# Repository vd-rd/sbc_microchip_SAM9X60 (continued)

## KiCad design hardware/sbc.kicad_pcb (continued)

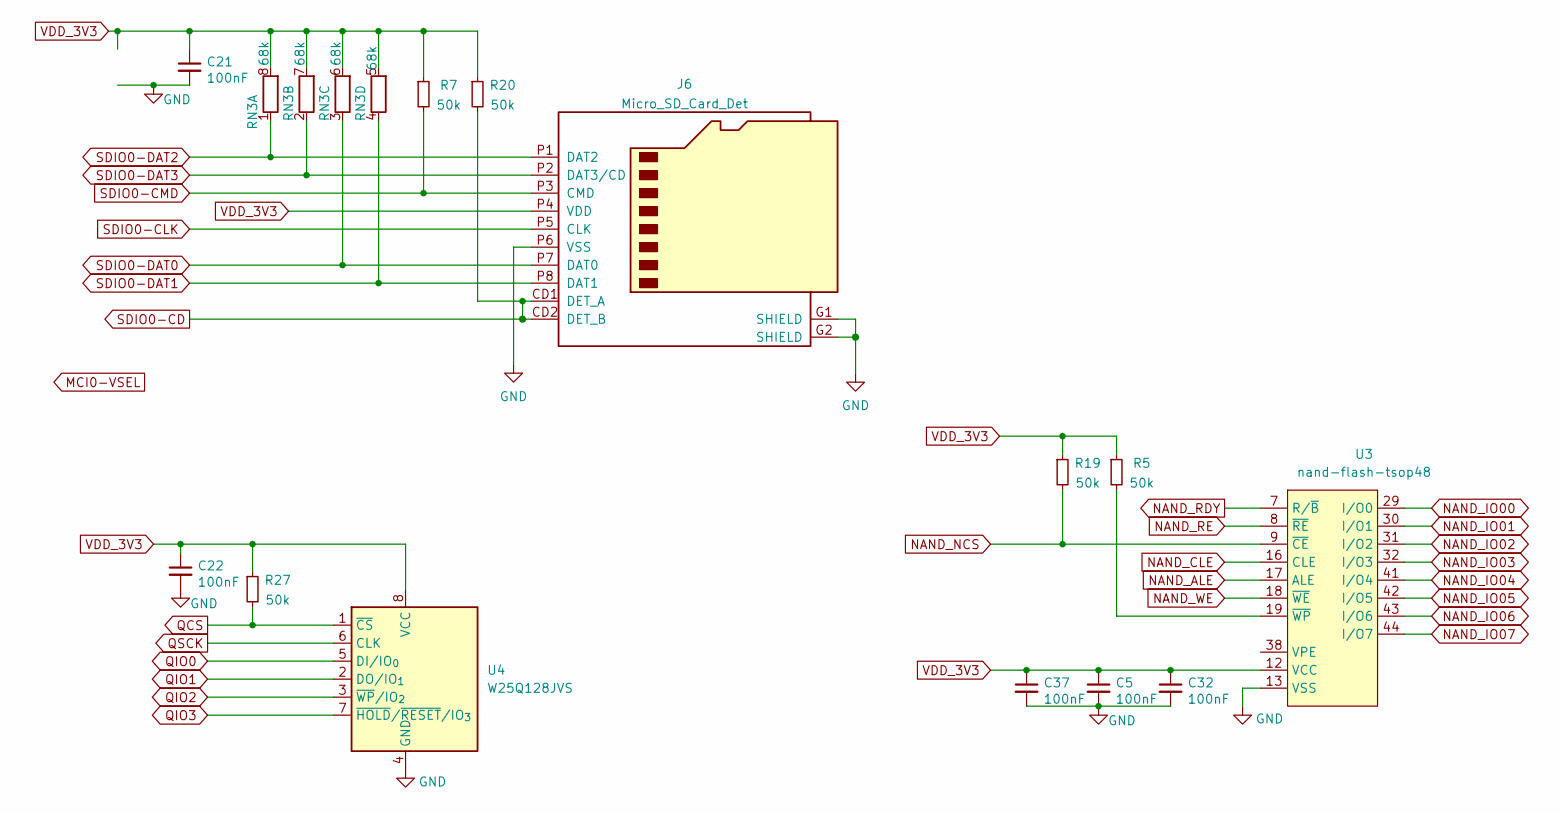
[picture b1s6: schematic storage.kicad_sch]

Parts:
C5, C21, C22, C32, C37: 100nF; C_0402_1005Metric
J6: Micro_SD_Card_Det; MEM20610118800A
R5, R7, R19, R20, R27: 50k; R_0402_1005Metric
RN3: 68k; R_Array_Concave_4x0402
U3: nand-flash-tsop48; TSOP-I-48_18.4x12mm_P0.5mm
U4: W25Q128JVS; SOIC-8_5.3x5.3mm_P1.27mm

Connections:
NAND_ALE: U3.17 (ALE); also elsewhere on the board
NAND_CLE: U3.16 (CLE); also elsewhere on the board
NAND_IO00: U3.29 (I/O0); also elsewhere on the board
NAND_IO01: U3.30 (I/O1); also elsewhere on the board
NAND_IO02: U3.31 (I/O2); also elsewhere on the board
NAND_IO03: U3.32 (I/O3); also elsewhere on the board
NAND_IO04: U3.41 (I/O4); also elsewhere on the board
NAND_IO05: U3.42 (I/O5); also elsewhere on the board
NAND_IO06: U3.43 (I/O6); also elsewhere on the board
NAND_IO07: U3.44 (I/O7); also elsewhere on the board
NAND_NCS: R19.2, U3.9 (~CE); also elsewhere on the board
NAND_RDY: U3.7 (R/~B); also elsewhere on the board
NAND_RE: U3.8 (~RE); also elsewhere on the board
NAND_WE: U3.18 (~WE); also elsewhere on the board
unnamed: R5.2, U3.19 (~WP)
QCS: R27.2, U4.1 (~CS); also elsewhere on the board
QIO0: U4.5 (DI/IO_{0}); also elsewhere on the board
QIO1: U4.2 (DO/IO_{1}); also elsewhere on the board
QIO2: U4.3 (~WP/IO_{2}); also elsewhere on the board
QIO3: U4.7 (~HOLD/~RESET/IO_{3}); also elsewhere on the board
QSCK: U4.6 (CLK); also elsewhere on the board
SDIO0-CD: J6.CD1 (DET_A), J6.CD2 (DET_B), R20.2; also elsewhere on the board
SDIO0-CLK: J6.P5 (CLK); also elsewhere on the board
SDIO0-CMD: J6.P3 (CMD), R7.2; also elsewhere on the board
SDIO0-DAT0: J6.P7 (DAT0), RN3.3 (R3.1); also elsewhere on the board
SDIO0-DAT1: J6.P8 (DAT1), RN3.4 (R4.1); also elsewhere on the board
SDIO0-DAT2: J6.P1 (DAT2), RN3.1 (R1.1); also elsewhere on the board
SDIO0-DAT3: J6.P2 (DAT3/CD), RN3.2 (R2.1); also elsewhere on the board
VDD_3V3: C5.1, C21.1, C22.1, C32.1, C37.1, J6.P4 (VDD), R5.1, R7.1, R19.1, R20.1, R27.1, RN3.5 (R4.2), RN3.6 (R3.2), RN3.7 (R2.2), RN3.8 (R1.2), U3.12 (VCC), U3.34 (VCC), U3.37 (VCC), U3.39 (VCC), U4.8 (VCC); also elsewhere on the board

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
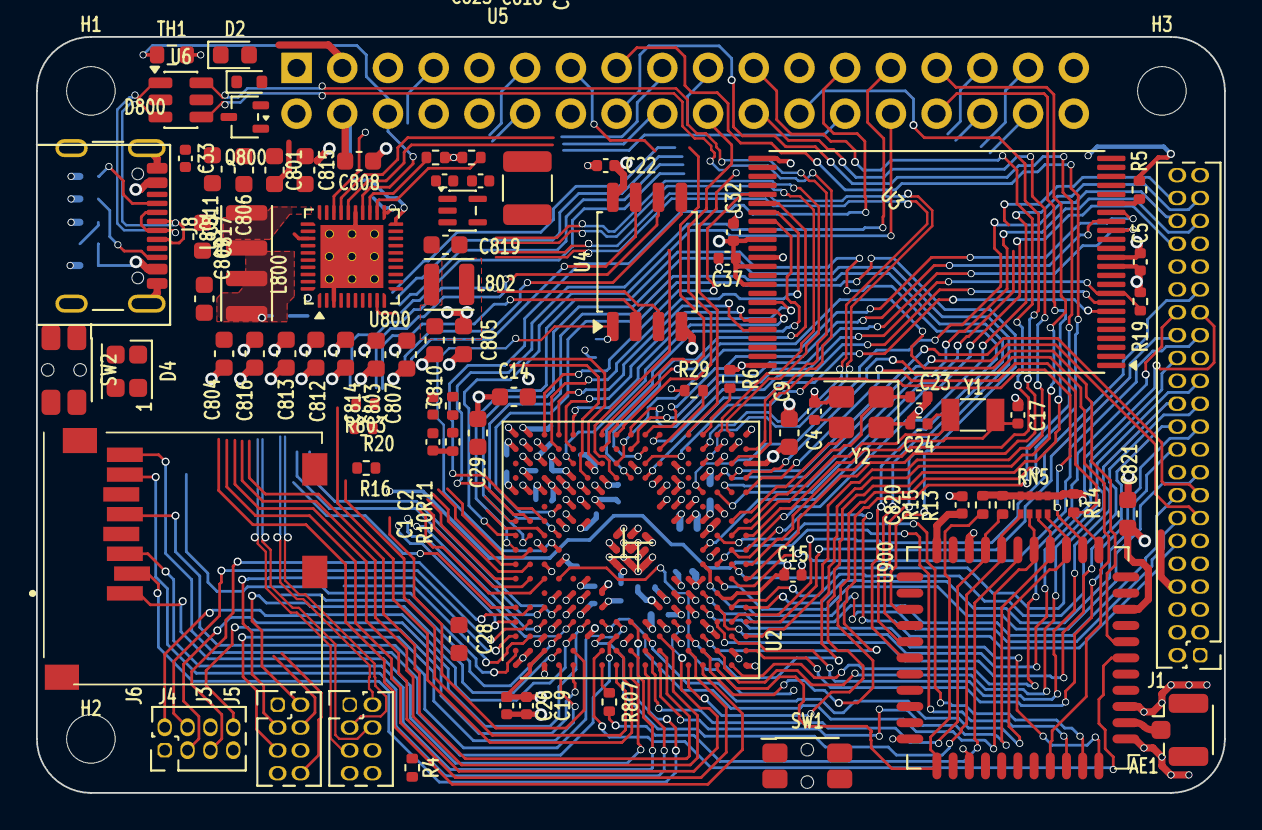
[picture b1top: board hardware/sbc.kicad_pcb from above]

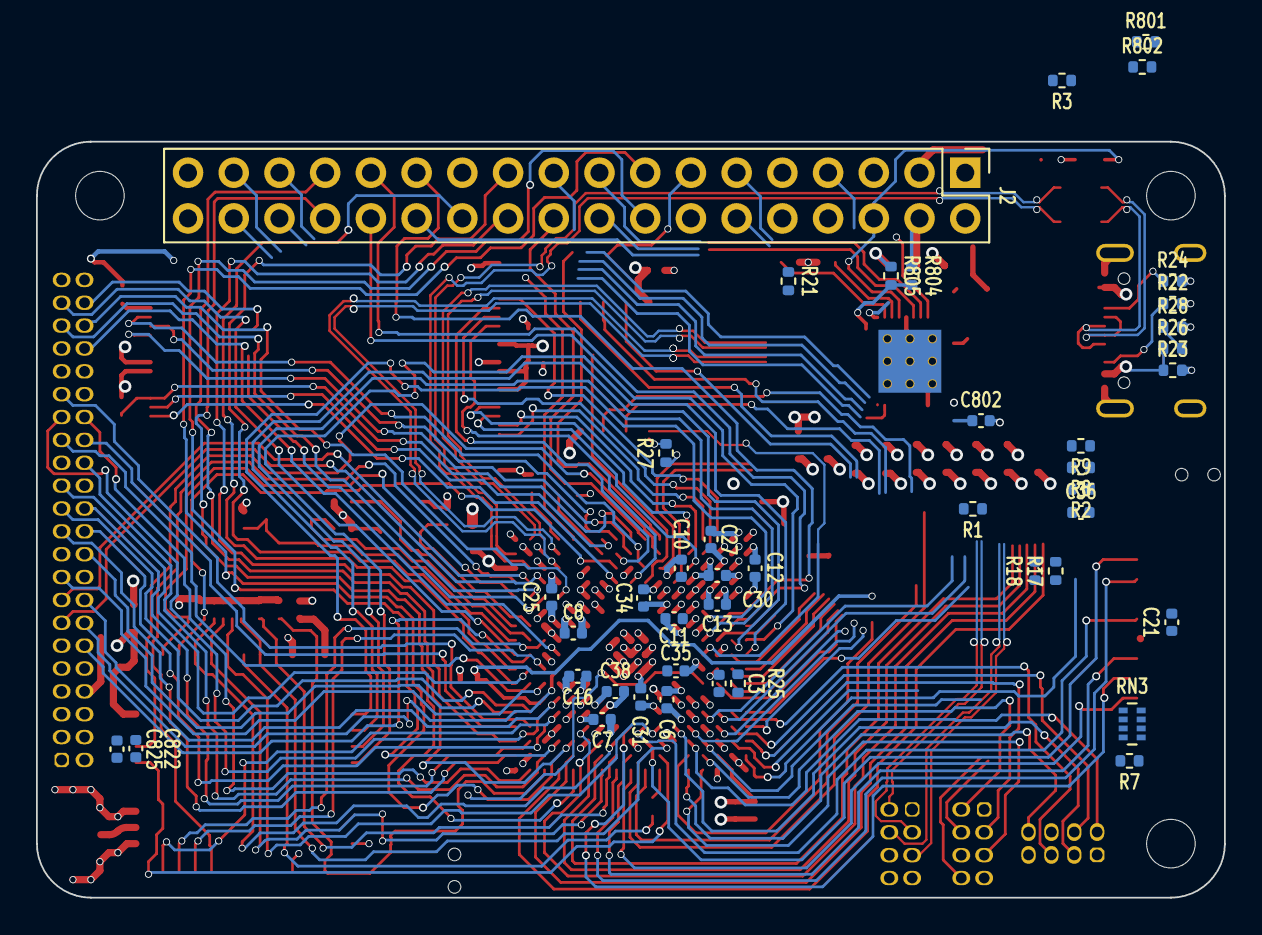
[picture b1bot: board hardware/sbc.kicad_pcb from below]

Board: 4 copper layers, 66.0 x 42.0 mm, 129 parts (43 on the bottom side), 165 nets.

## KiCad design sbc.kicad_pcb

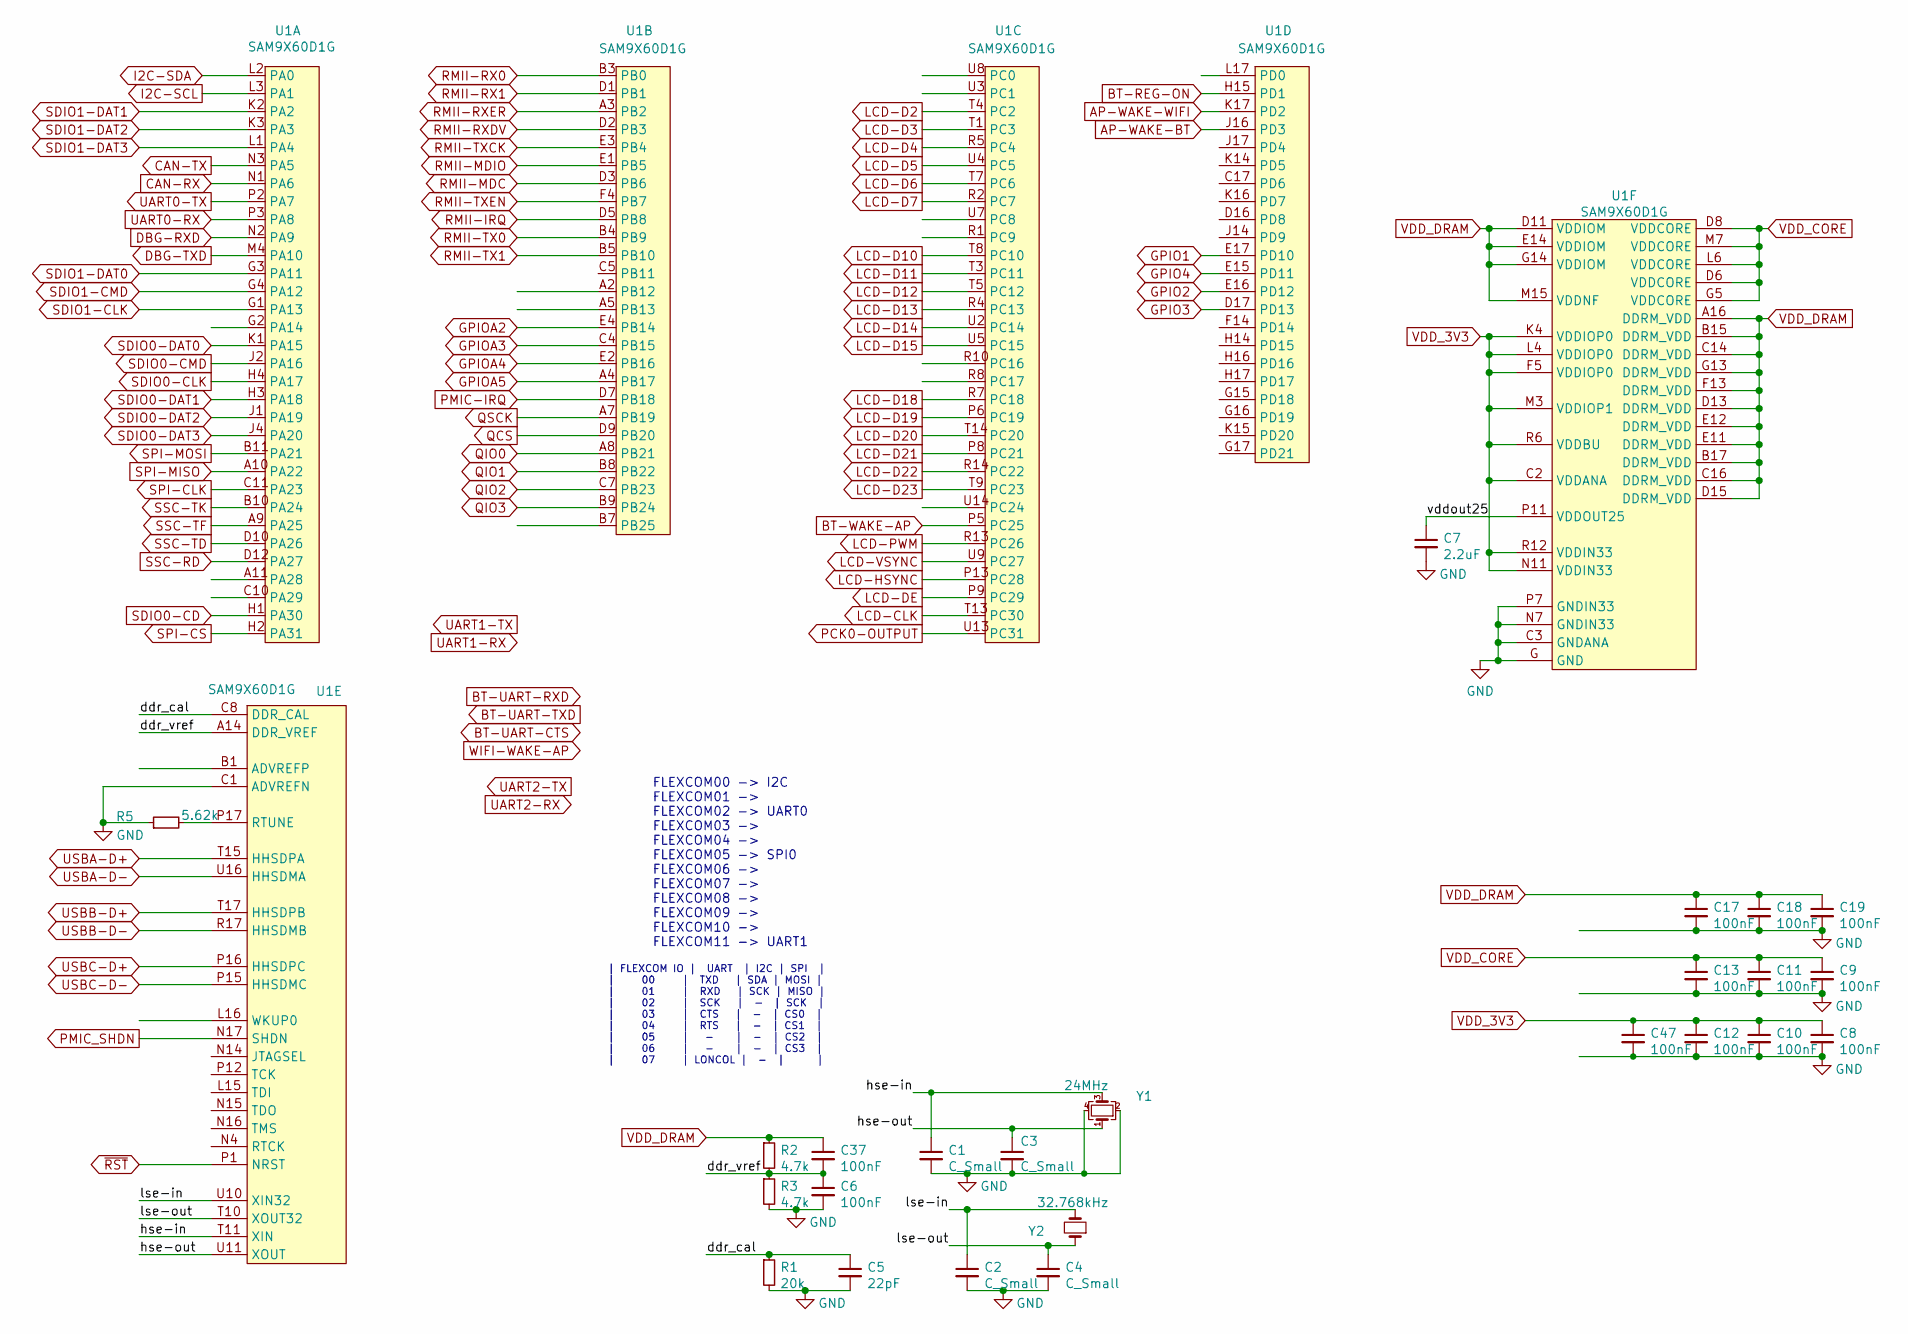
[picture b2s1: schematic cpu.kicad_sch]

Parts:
C1, C2, C3, C4: C_Small; C_0402_1005Metric
C5: 22pF; C_0402_1005Metric
C6, C8, C9, C10, C11, C12, C13, C17, C18, C19, C37, C47: 100nF; C_0402_1005Metric
C7: 2.2uF; C_0402_1005Metric
R1: 20k; R_0402_1005Metric
R2, R3: 4.7k; R_0402_1005Metric
R5: 5.62k; R_0402_1005Metric
U1: SAM9X60D1G
Y1: 24MHz; Crystal_SMD_3225-4Pin_3.2x2.5mm
Y2: 32.768kHz; Crystal_SMD_3215-2Pin_3.2x1.5mm

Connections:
/cpu/ddr_cal: C5.1, R1.1, U1.C8 (DDR_CAL)
/cpu/ddr_vref: C6.1, C37.2, R2.2, R3.1, U1.A14 (DDR_VREF)
/cpu/hse-in: C1.1, U1.T11 (XIN), Y1.3
/cpu/hse-out: C3.1, U1.U11 (XOUT), Y1.1
/cpu/lse-in: C2.1, U1.U10 (XIN32), Y2.2
/cpu/lse-out: C4.1, U1.T10 (XOUT32), Y2.1
/cpu/vddout25: C7.1, U1.P11 (VDDOUT25)
AP-WAKE-BT: U1.J16 (PD3); also elsewhere on the board
AP-WAKE-WIFI: U1.K17 (PD2); also elsewhere on the board
BT-REG-ON: U1.H15 (PD1); also elsewhere on the board
BT-WAKE-AP: U1.P5 (PC25); also elsewhere on the board
CAN-RX: U1.N1 (PA6); also elsewhere on the board
CAN-TX: U1.N3 (PA5); also elsewhere on the board
DBG-RXD: U1.N2 (PA9); also elsewhere on the board
DBG-TXD: U1.M4 (PA10); also elsewhere on the board
GND: C1.2, C2.2, C3.2, C4.2, C5.2, C6.2, C7.2, C8.2, C9.2, C10.2, C11.2, C12.2, C13.2, C17.2, C18.2, C19.2, C47.2, R1.2, R3.2, R5.1, U1.C1 (ADVREFN), U1.C3 (GNDANA), U1.G (GND), U1.N7 (GNDIN33), U1.P7 (GNDIN33), Y1.2, Y1.4; also elsewhere on the board
GPIO1: U1.E17 (PD10); also elsewhere on the board
GPIO2: U1.E16 (PD12); also elsewhere on the board
GPIO3: U1.D17 (PD13); also elsewhere on the board
GPIO4: U1.E15 (PD11); also elsewhere on the board
GPIOA2: U1.E4 (PB14); also elsewhere on the board
GPIOA3: U1.C4 (PB15); also elsewhere on the board
GPIOA4: U1.E2 (PB16); also elsewhere on the board
GPIOA5: U1.A4 (PB17); also elsewhere on the board
I2C-SCL: U1.L3 (PA1); also elsewhere on the board
I2C-SDA: U1.L2 (PA0); also elsewhere on the board
LCD-CLK: U1.T13 (PC30); also elsewhere on the board
LCD-D2: U1.T4 (PC2); also elsewhere on the board
LCD-D3: U1.T1 (PC3); also elsewhere on the board
LCD-D4: U1.R5 (PC4); also elsewhere on the board
LCD-D5: U1.U4 (PC5); also elsewhere on the board
LCD-D6: U1.T7 (PC6); also elsewhere on the board
LCD-D7: U1.R2 (PC7); also elsewhere on the board
LCD-D10: U1.T8 (PC10); also elsewhere on the board
LCD-D11: U1.T3 (PC11); also elsewhere on the board
LCD-D12: U1.T5 (PC12); also elsewhere on the board
LCD-D13: U1.R4 (PC13); also elsewhere on the board
LCD-D14: U1.U2 (PC14); also elsewhere on the board
LCD-D15: U1.U5 (PC15); also elsewhere on the board
LCD-D18: U1.R7 (PC18); also elsewhere on the board
LCD-D19: U1.P6 (PC19); also elsewhere on the board
LCD-D20: U1.T14 (PC20); also elsewhere on the board
LCD-D21: U1.P8 (PC21); also elsewhere on the board
LCD-D22: U1.R14 (PC22); also elsewhere on the board
LCD-D23: U1.T9 (PC23); also elsewhere on the board
LCD-DE: U1.P9 (PC29); also elsewhere on the board
LCD-HSYNC: U1.P13 (PC28); also elsewhere on the board
LCD-PWM: U1.R13 (PC26)
LCD-VSYNC: U1.U9 (PC27); also elsewhere on the board
unnamed: R5.2, U1.P17 (RTUNE)
PCK0-OUTPUT: U1.U13 (PC31); also elsewhere on the board
PMIC-IRQ: U1.D7 (PB18); also elsewhere on the board
PMIC_SHDN: U1.N17 (SHDN)
QCS: U1.D9 (PB20); also elsewhere on the board
QIO0: U1.A8 (PB21); also elsewhere on the board
QIO1: U1.B8 (PB22); also elsewhere on the board
QIO2: U1.C7 (PB23); also elsewhere on the board
QIO3: U1.B9 (PB24); also elsewhere on the board
QSCK: U1.A7 (PB19); also elsewhere on the board
RMII-IRQ: U1.D5 (PB8)
RMII-MDC: U1.D3 (PB6); also elsewhere on the board
RMII-MDIO: U1.E1 (PB5); also elsewhere on the board
RMII-RX0: U1.B3 (PB0); also elsewhere on the board
RMII-RX1: U1.D1 (PB1); also elsewhere on the board
RMII-RXDV: U1.D2 (PB3); also elsewhere on the board
RMII-RXER: U1.A3 (PB2); also elsewhere on the board
RMII-TX0: U1.B4 (PB9); also elsewhere on the board
RMII-TX1: U1.B5 (PB10); also elsewhere on the board
RMII-TXCK: U1.E3 (PB4); also elsewhere on the board
RMII-TXEN: U1.F4 (PB7); also elsewhere on the board
SDIO0-CD: U1.H1 (PA30); also elsewhere on the board
SDIO0-CLK: U1.H4 (PA17); also elsewhere on the board
SDIO0-CMD: U1.J2 (PA16); also elsewhere on the board
SDIO0-DAT0: U1.K1 (PA15); also elsewhere on the board
SDIO0-DAT1: U1.H3 (PA18); also elsewhere on the board
SDIO0-DAT2: U1.J1 (PA19); also elsewhere on the board
SDIO0-DAT3: U1.J4 (PA20); also elsewhere on the board
SDIO1-CLK: U1.G1 (PA13); also elsewhere on the board
SDIO1-CMD: U1.G4 (PA12); also elsewhere on the board
SDIO1-DAT0: U1.G3 (PA11); also elsewhere on the board
SDIO1-DAT1: U1.K2 (PA2); also elsewhere on the board
SDIO1-DAT2: U1.K3 (PA3); also elsewhere on the board
SDIO1-DAT3: U1.L1 (PA4); also elsewhere on the board
SPI-CLK: U1.C11 (PA23); also elsewhere on the board
SPI-CS: U1.H2 (PA31); also elsewhere on the board
SPI-MISO: U1.A10 (PA22); also elsewhere on the board
SPI-MOSI: U1.B11 (PA21); also elsewhere on the board
SSC-RD: U1.D12 (PA27); also elsewhere on the board
SSC-TD: U1.D10 (PA26); also elsewhere on the board
SSC-TF: U1.A9 (PA25); also elsewhere on the board
SSC-TK: U1.B10 (PA24); also elsewhere on the board
UART0-RX: U1.P3 (PA8)
UART0-TX: U1.P2 (PA7)
USBA-D+: U1.T15 (HHSDPA); also elsewhere on the board
USBA-D-: U1.U16 (HHSDMA); also elsewhere on the board
USBB-D+: U1.T17 (HHSDPB)
USBB-D-: U1.R17 (HHSDMB)
USBC-D+: U1.P16 (HHSDPC)
USBC-D-: U1.P15 (HHSDMC)
VDD_3V3: C8.1, C10.1, C12.1, C47.1, U1.C2 (VDDANA), U1.F5 (VDDIOP0), U1.K4 (VDDIOP0), U1.L4 (VDDIOP0), U1.M3 (VDDIOP1), U1.N11 (VDDIN33), U1.R6 (VDDBU), U1.R12 (VDDIN33); also elsewhere on the board
VDD_CORE: C9.1, C11.1, C13.1, U1.D6 (VDDCORE), U1.D8 (VDDCORE), U1.G5 (VDDCORE), U1.L6 (VDDCORE), U1.M7 (VDDCORE); also elsewhere on the board
VDD_DRAM: C17.1, C18.1, C19.1, C37.1, R2.1, U1.A16 (DDRM_VDD), U1.B15 (DDRM_VDD), U1.B17 (DDRM_VDD), U1.C14 (DDRM_VDD), U1.C16 (DDRM_VDD), U1.D11 (VDDIOM), U1.D13 (DDRM_VDD), U1.D15 (DDRM_VDD), U1.E11 (DDRM_VDD), U1.E12 (DDRM_VDD), U1.E14 (VDDIOM), U1.F13 (DDRM_VDD), U1.G13 (DDRM_VDD), U1.G14 (VDDIOM), U1.M15 (VDDNF); also elsewhere on the board
~RST: U1.P1 (NRST); also elsewhere on the board

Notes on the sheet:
| FLEXCOM IO | UART | I2C | SPI | | 00 | TXD | SDA | MOSI | | 01 | RXD | SCK | MISO | | 02 | SCK | - | SCK | | 03 | CTS | - | CS0 | | 04 | RTS | - | CS1 | | 05 | - | - | CS2 | | 06 | - | - | CS3 | | 07 | LONCOL | - | |
FLEXCOM00 -> I2C FLEXCOM01 -> FLEXCOM02 -> UART0 FLEXCOM03 -> FLEXCOM04 -> FLEXCOM05 -> SPI0 FLEXCOM06 -> FLEXCOM07 -> FLEXCOM08 -> FLEXCOM09 -> FLEXCOM10 -> FLEXCOM11 -> UART1

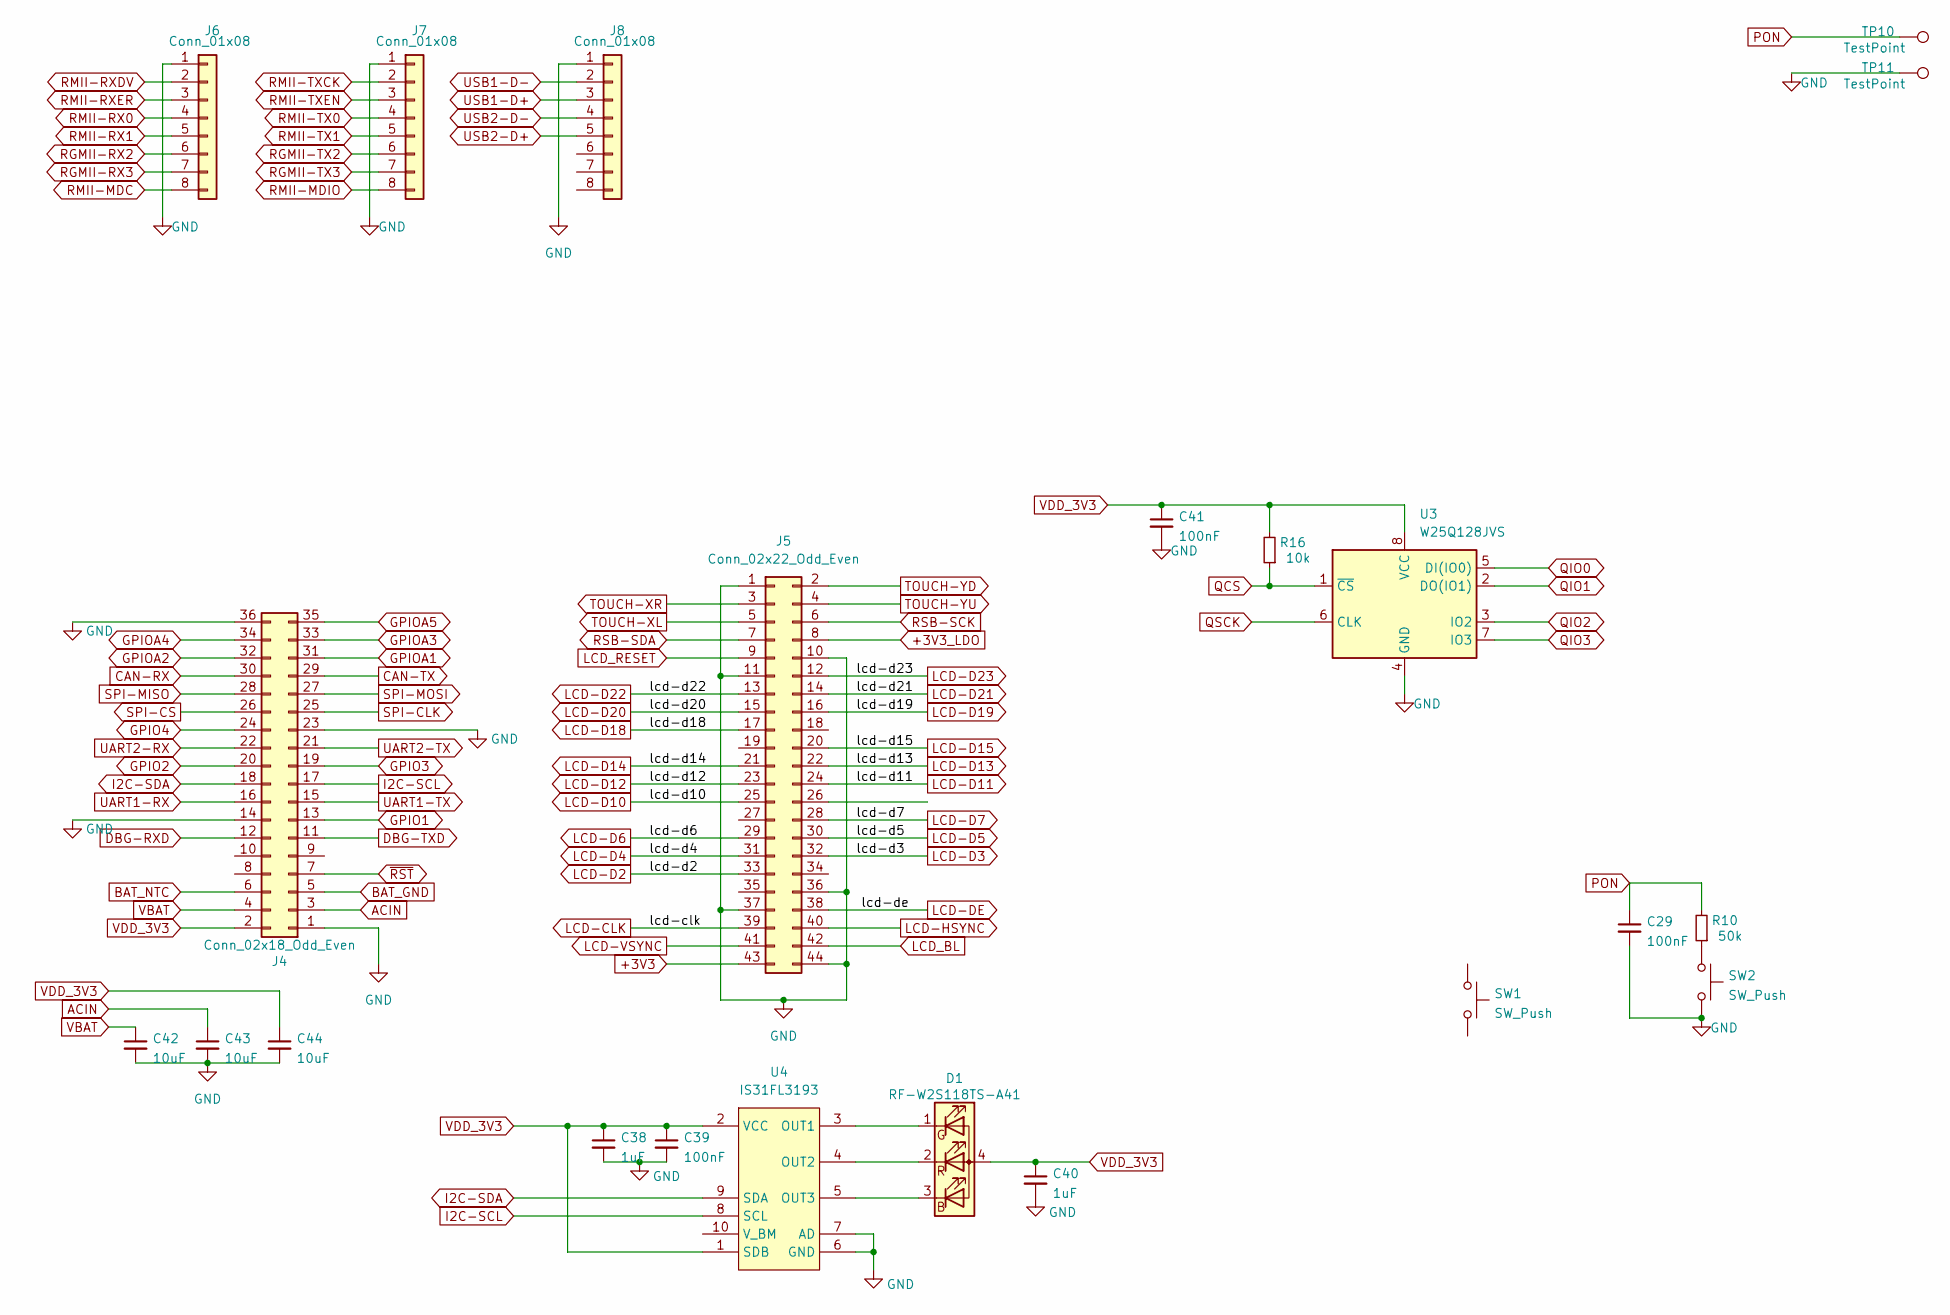
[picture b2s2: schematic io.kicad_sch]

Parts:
C29, C39, C41: 100nF; C_0402_1005Metric
C38, C40: 1uF; C_0402_1005Metric
C42, C43, C44: 10uF; C_0805_2012Metric
D1: RF-W2S118TS-A41; rgb-1204
J4: Conn_02x18_Odd_Even; PinHeader_2x18_P2.54mm_Vertical
J5: Conn_02x22_Odd_Even; PinHeader_2x22_P1.27mm_Vertical
J6, J7, J8: Conn_01x08; PinHeader_2x04_P1.27mm_Vertical
R10: 50k; R_0402_1005Metric
R16: 10k; R_0402_1005Metric
SW1, SW2: SW_Push; SW_SPST_EVQP7C
TP10, TP11: TestPoint; TestPoint_Pad_D1.0mm
U3: W25Q128JVS; SOIC-8_5.23x5.23mm_P1.27mm
U4: IS31FL3193; DFN-10-1EP_3x3mm_P0.5mm_EP1.7x2.5mm

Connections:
+3V3: J5.43
+3V3_LDO: J5.8
ACIN: C43.1, J4.3; also elsewhere on the board
BAT_GND: J4.5
BAT_NTC: J4.6; also elsewhere on the board
CAN-RX: J4.30; also elsewhere on the board
CAN-TX: J4.29; also elsewhere on the board
DBG-RXD: J4.12; also elsewhere on the board
DBG-TXD: J4.11; also elsewhere on the board
GND: C29.2, C38.2, C39.2, C40.2, C41.2, C42.2, C43.2, C44.2, J4.1, J4.14, J4.23, J4.36, J5.1, J5.10, J5.11, J5.36, J5.37, J5.44, J6.1, J7.1, J8.1, SW2.2, TP11.1, U3.4 (GND), U4.6 (GND), U4.7 (AD), U4.11 (GND); also elsewhere on the board
GPIO1: J4.13; also elsewhere on the board
GPIO2: J4.20; also elsewhere on the board
GPIO3: J4.19; also elsewhere on the board
GPIO4: J4.24; also elsewhere on the board
GPIOA1: J4.31
GPIOA2: J4.32; also elsewhere on the board
GPIOA3: J4.33; also elsewhere on the board
GPIOA4: J4.34; also elsewhere on the board
GPIOA5: J4.35; also elsewhere on the board
I2C-SCL: J4.17, U4.8 (SCL); also elsewhere on the board
I2C-SDA: J4.18, U4.9 (SDA); also elsewhere on the board
LCD-CLK: J5.39; also elsewhere on the board
LCD-D2: J5.33; also elsewhere on the board
LCD-D3: J5.32; also elsewhere on the board
LCD-D4: J5.31; also elsewhere on the board
LCD-D5: J5.30; also elsewhere on the board
LCD-D6: J5.29; also elsewhere on the board
LCD-D7: J5.28; also elsewhere on the board
LCD-D10: J5.25; also elsewhere on the board
LCD-D11: J5.24; also elsewhere on the board
LCD-D12: J5.23; also elsewhere on the board
LCD-D13: J5.22; also elsewhere on the board
LCD-D14: J5.21; also elsewhere on the board
LCD-D15: J5.20; also elsewhere on the board
LCD-D18: J5.17; also elsewhere on the board
LCD-D19: J5.16; also elsewhere on the board
LCD-D20: J5.15; also elsewhere on the board
LCD-D21: J5.14; also elsewhere on the board
LCD-D22: J5.13; also elsewhere on the board
LCD-D23: J5.12; also elsewhere on the board
LCD-DE: J5.38; also elsewhere on the board
LCD-HSYNC: J5.40; also elsewhere on the board
LCD-VSYNC: J5.41; also elsewhere on the board
LCD_BL: J5.42
LCD_RESET: J5.9
unnamed: D1.3 (BK), U4.5 (OUT3)
unnamed: D1.1 (GK), U4.3 (OUT1)
unnamed: D1.2 (RK), U4.4 (OUT2)
unnamed: R10.1, SW2.1
PON: C29.1, R10.2, TP10.1; also elsewhere on the board
QCS: R16.1, U3.1 (~CS); also elsewhere on the board
QIO0: U3.5 (DI(IO0)); also elsewhere on the board
QIO1: U3.2 (DO(IO1)); also elsewhere on the board
QIO2: U3.3 (IO2); also elsewhere on the board
QIO3: U3.7 (IO3); also elsewhere on the board
QSCK: U3.6 (CLK); also elsewhere on the board
RGMII-RX2: J6.6
RGMII-RX3: J6.7
RGMII-TX2: J7.6
RGMII-TX3: J7.7
RMII-MDC: J6.8; also elsewhere on the board
RMII-MDIO: J7.8; also elsewhere on the board
RMII-RX0: J6.4; also elsewhere on the board
RMII-RX1: J6.5; also elsewhere on the board
RMII-RXDV: J6.2; also elsewhere on the board
RMII-RXER: J6.3; also elsewhere on the board
RMII-TX0: J7.4; also elsewhere on the board
RMII-TX1: J7.5; also elsewhere on the board
RMII-TXCK: J7.2; also elsewhere on the board
RMII-TXEN: J7.3; also elsewhere on the board
RSB-SCK: J5.6
RSB-SDA: J5.7
SPI-CLK: J4.25; also elsewhere on the board
SPI-CS: J4.26; also elsewhere on the board
SPI-MISO: J4.28; also elsewhere on the board
SPI-MOSI: J4.27; also elsewhere on the board
TOUCH-XL: J5.5
TOUCH-XR: J5.3
TOUCH-YD: J5.2
TOUCH-YU: J5.4
UART1-RX: J4.16
UART1-TX: J4.15
UART2-RX: J4.22
UART2-TX: J4.21
USB1-D+: J8.3
USB1-D-: J8.2
USB2-D+: J8.5
USB2-D-: J8.4
VBAT: C42.1, J4.4; also elsewhere on the board
VDD_3V3: C38.1, C39.1, C40.1, C41.1, C44.1, D1.4 (A), J4.2, R16.2, U3.8 (VCC), U4.1 (SDB), U4.2 (VCC); also elsewhere on the board
~RST: J4.7; also elsewhere on the board

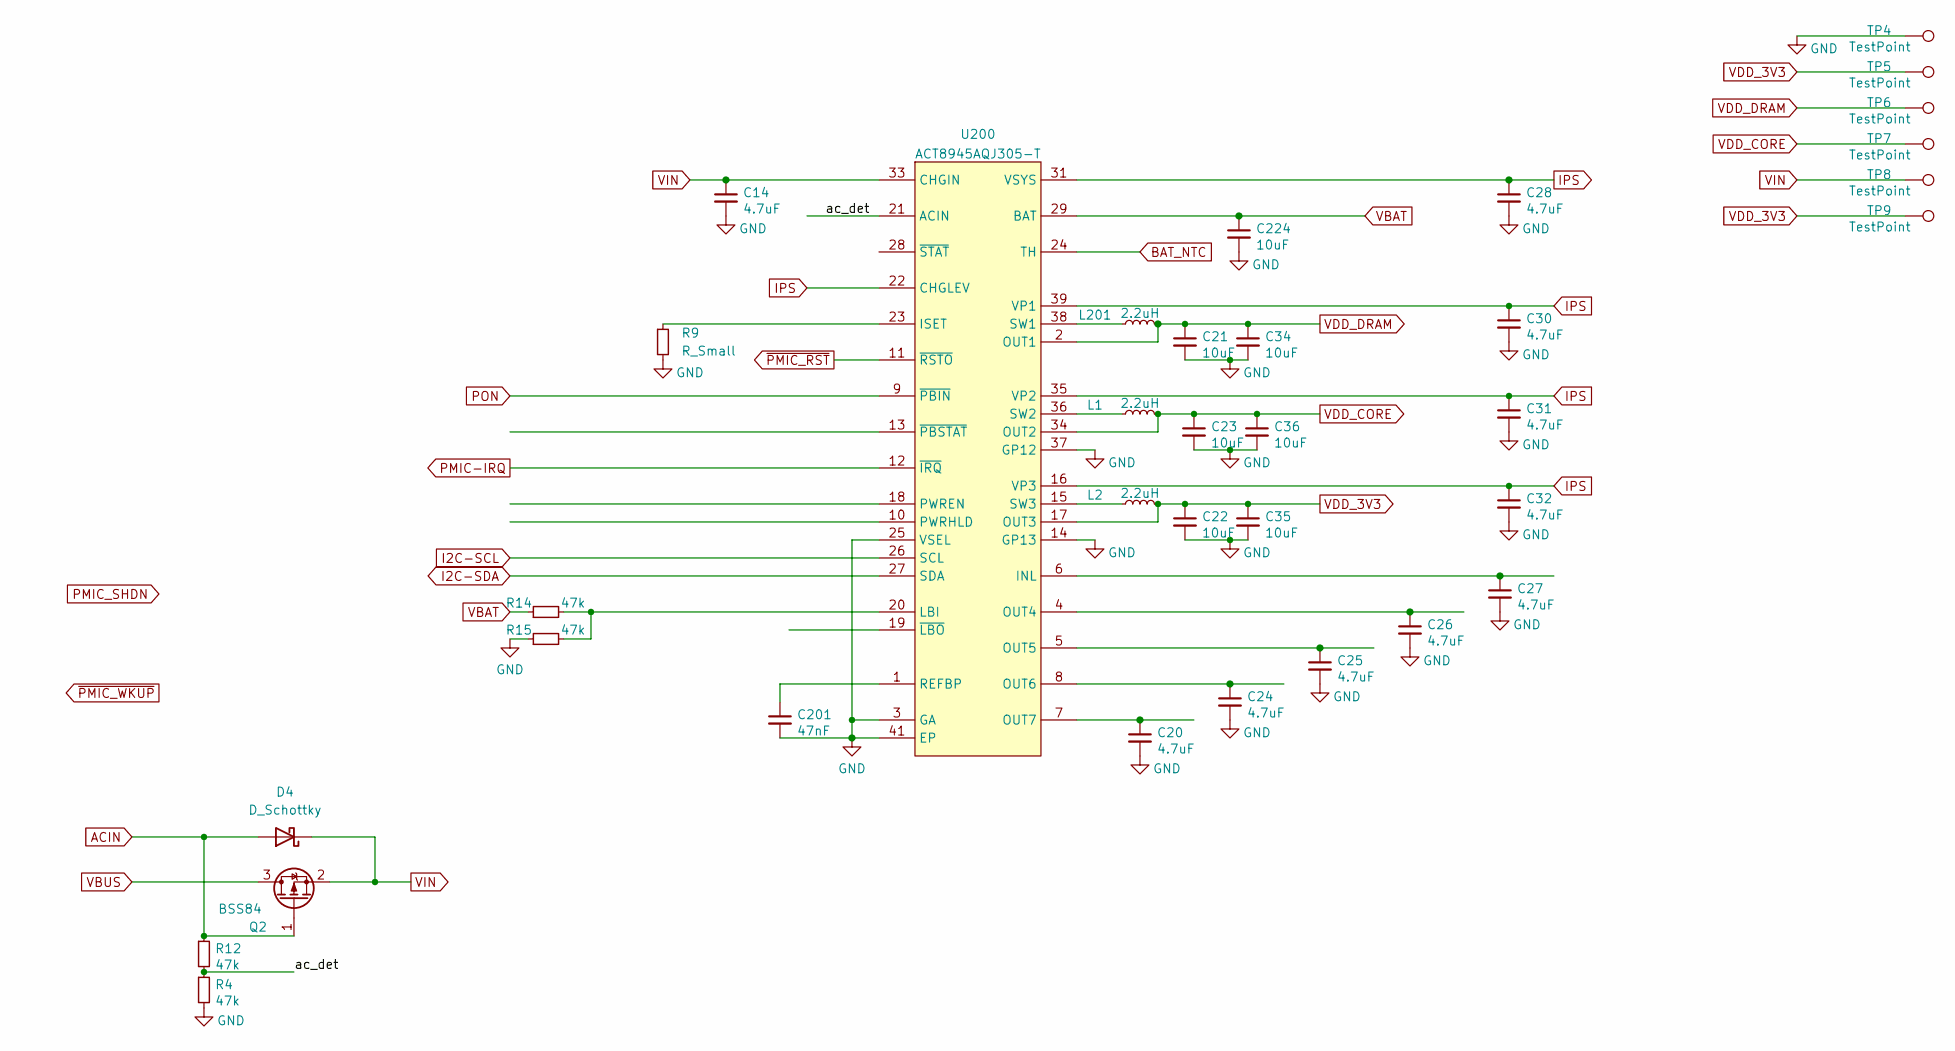
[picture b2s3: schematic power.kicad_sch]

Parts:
C14, C20, C24, C25, C26, C27: 4.7uF; C_0603_1608Metric
C21, C22, C23, C34, C35, C36, C224: 10uF; C_0603_1608Metric
C28, C30, C31, C32: 4.7uF; C_0402_1005Metric
C201: 47nF; C_0402_1005Metric
D4: D_Schottky; D_SOD-523
L1, L2, L201: 2.2uH; L_Wuerth_MAPI-2510
Q2: BSS84; SOT-323_SC-70
R4, R12, R14, R15: 47k; R_0402_1005Metric
R9: R_Small; R_0402_1005Metric
TP4, TP5, TP6, TP7, TP8, TP9: TestPoint; TestPoint_Pad_D1.0mm
U200: ACT8945AQJ305-T; TQFN-40-1EP_5x5mm_P0.4mm_EP3.5x3.5mm_ThermalVias

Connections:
/power/ac_det: R4.1, R12.2, U200.21 (ACIN)
ACIN: D4.2 (A), Q2.1 (G), R12.1; also elsewhere on the board
BAT_NTC: U200.24 (TH); also elsewhere on the board
GND: C14.2, C20.2, C21.2, C22.2, C23.2, C24.2, C25.2, C26.2, C27.2, C28.2, C30.2, C31.2, C32.2, C34.2, C35.2, C36.2, C201.2, C224.2, R4.2, R9.2, R15.1, TP4.1, U200.3 (GA), U200.14 (GP13), U200.25 (VSEL), U200.37 (GP12), U200.41 (EP); also elsewhere on the board
I2C-SCL: U200.26 (SCL); also elsewhere on the board
I2C-SDA: U200.27 (SDA); also elsewhere on the board
IPS: C28.1, C30.1, C31.1, C32.1, U200.16 (VP3), U200.22 (CHGLEV), U200.31 (VSYS), U200.32 (VSYS), U200.35 (VP2), U200.39 (VP1)
unnamed: C27.1, U200.6 (INL)
unnamed: R9.1, U200.23 (ISET)
unnamed: R14.2, R15.2, U200.20 (LBI)
unnamed: C26.1, U200.4 (OUT4)
unnamed: C25.1, U200.5 (OUT5)
unnamed: C24.1, U200.8 (OUT6)
unnamed: C20.1, U200.7 (OUT7)
unnamed: C201.1, U200.1 (REFBP)
unnamed: L201.1, U200.38 (SW1)
unnamed: L1.1, U200.36 (SW2)
unnamed: L2.1, U200.15 (SW3)
PMIC-IRQ: U200.12 (~IRQ); also elsewhere on the board
PON: U200.9 (~PBIN); also elsewhere on the board
VBAT: C224.1, R14.1, U200.29 (BAT), U200.30 (BAT); also elsewhere on the board
VBUS: Q2.3 (D); also elsewhere on the board
VDD_3V3: C22.1, C35.1, L2.2, TP5.1, TP9.1, U200.17 (OUT3); also elsewhere on the board
VDD_CORE: C23.1, C36.1, L1.2, TP7.1, U200.34 (OUT2); also elsewhere on the board
VDD_DRAM: C21.1, C34.1, L201.2, TP6.1, U200.2 (OUT1); also elsewhere on the board
VIN: C14.1, D4.1 (K), Q2.2 (S), TP8.1, U200.33 (CHGIN)
~PMIC_RST: U200.11 (~RSTO)

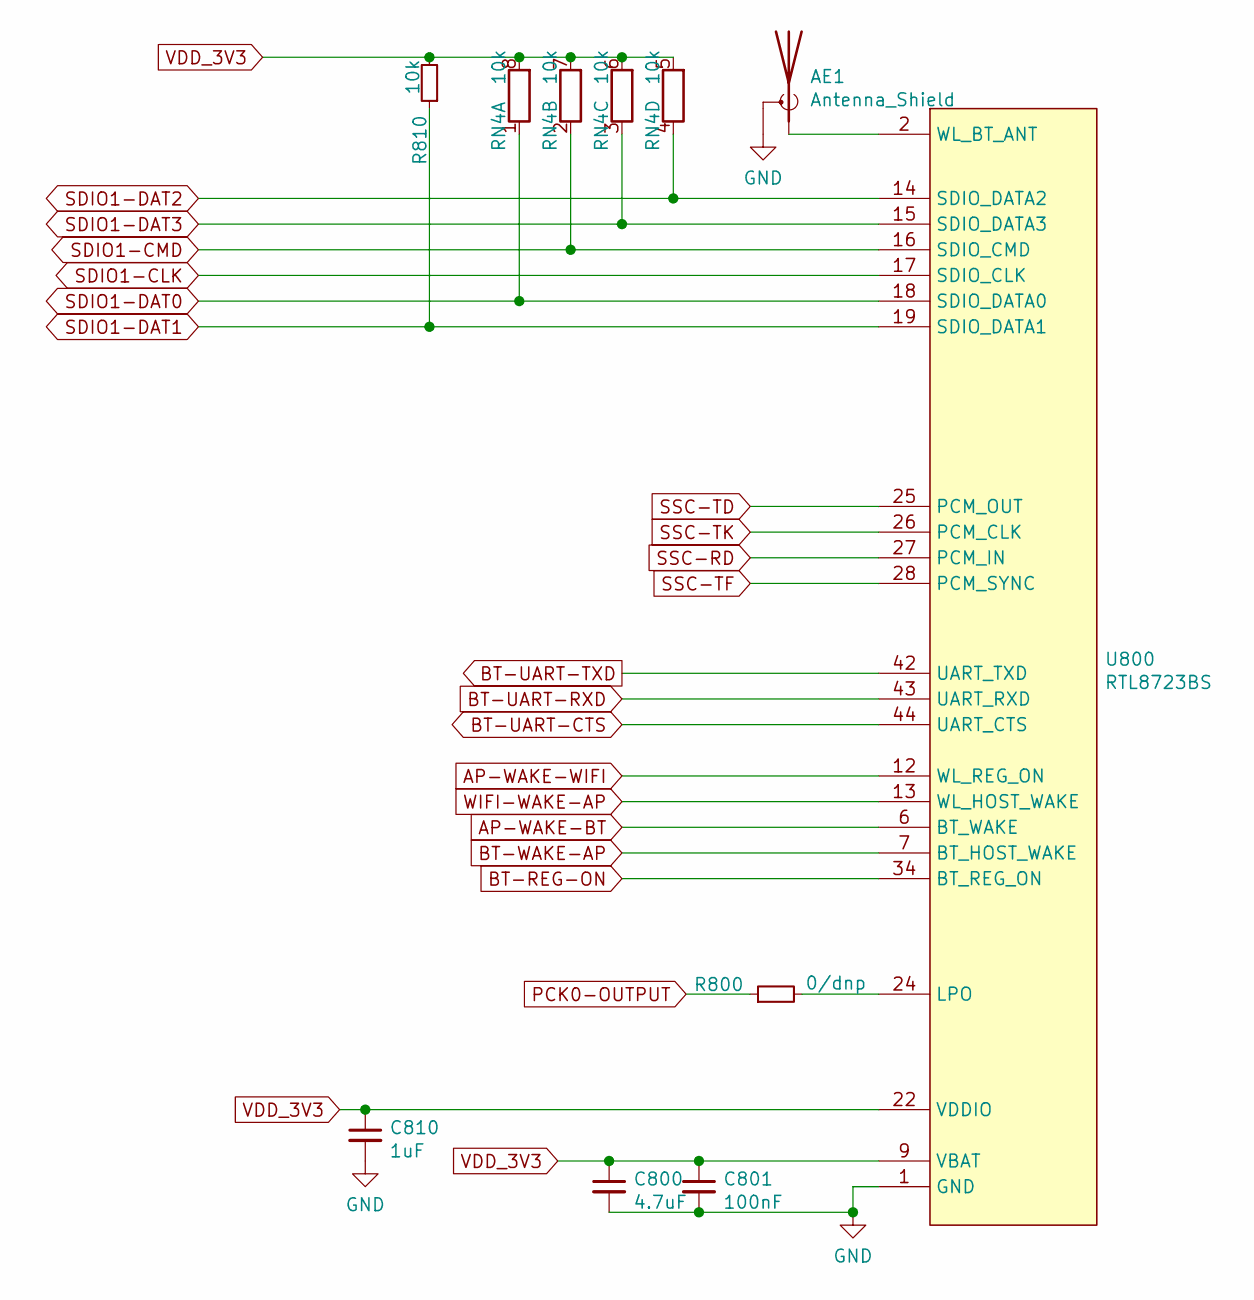
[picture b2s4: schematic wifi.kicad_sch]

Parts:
AE1: Antenna_Shield; U.FL_Hirose_U.FL-R-SMT-1_Vertical
C800: 4.7uF; C_0603_1608Metric
C801: 100nF; C_0402_1005Metric
C810: 1uF; C_0402_1005Metric
R800: 0/dnp; R_0402_1005Metric
R810: 10k; R_0402_1005Metric
RN4: 10k; R_Array_Convex_4x0402
U800: RTL8723BS; lga44_12x12mm_P0.9

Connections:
AP-WAKE-BT: U800.6 (BT_WAKE); also elsewhere on the board
AP-WAKE-WIFI: U800.12 (WL_REG_ON); also elsewhere on the board
BT-REG-ON: U800.34 (BT_REG_ON); also elsewhere on the board
BT-UART-CTS: U800.44 (UART_CTS)
BT-UART-RXD: U800.43 (UART_RXD)
BT-UART-TXD: U800.42 (UART_TXD)
BT-WAKE-AP: U800.7 (BT_HOST_WAKE); also elsewhere on the board
GND: AE1.2 (Shield), C800.2, C801.2, C810.2, U800.1 (GND), U800.3 (GND), U800.20 (GND), U800.31 (GND), U800.33 (GND), U800.36 (GND), U800.41 (GND); also elsewhere on the board
unnamed: AE1.1 (A), U800.2 (WL_BT_ANT)
unnamed: R800.2, U800.24 (LPO)
PCK0-OUTPUT: R800.1; also elsewhere on the board
SDIO1-CLK: U800.17 (SDIO_CLK); also elsewhere on the board
SDIO1-CMD: RN4.2 (R2.1), U800.16 (SDIO_CMD); also elsewhere on the board
SDIO1-DAT0: RN4.1 (R1.1), U800.18 (SDIO_DATA0); also elsewhere on the board
SDIO1-DAT1: R810.1, U800.19 (SDIO_DATA1); also elsewhere on the board
SDIO1-DAT2: RN4.4 (R4.1), U800.14 (SDIO_DATA2); also elsewhere on the board
SDIO1-DAT3: RN4.3 (R3.1), U800.15 (SDIO_DATA3); also elsewhere on the board
SSC-RD: U800.27 (PCM_IN); also elsewhere on the board
SSC-TD: U800.25 (PCM_OUT); also elsewhere on the board
SSC-TF: U800.28 (PCM_SYNC); also elsewhere on the board
SSC-TK: U800.26 (PCM_CLK); also elsewhere on the board
VDD_3V3: C800.1, C801.1, C810.1, R810.2, RN4.5 (R4.2), RN4.6 (R3.2), RN4.7 (R2.2), RN4.8 (R1.2), U800.9 (VBAT), U800.22 (VDDIO); also elsewhere on the board
WIFI-WAKE-AP: U800.13 (WL_HOST_WAKE)
